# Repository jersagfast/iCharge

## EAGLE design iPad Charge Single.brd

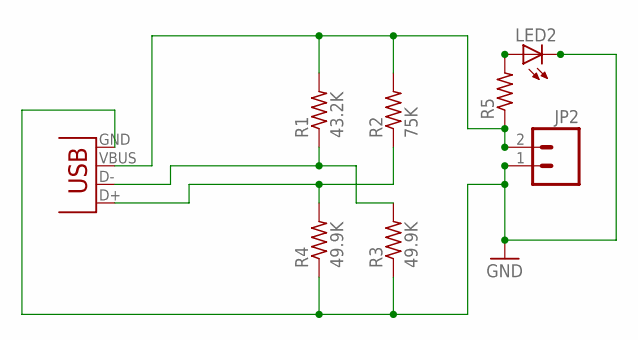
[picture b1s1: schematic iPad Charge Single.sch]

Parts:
JP2: M023.5MM; SCREWTERMINAL-3.5MM-2
LED2: LEDCHIP-LED0805; CHIP-LED0805
R1: 43.2K; R0805
R2: 75K; R0805
R3, R4: 49.9K; R0805
R5: R-US_R0805; R0805
X1: USB-A-S

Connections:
GND: JP2.1, LED2.C, R3.1, R4.1, X1.GND
unnamed: JP2.2, R1.2, R2.2, R5.1, X1.VBUS
unnamed: LED2.A, R5.2
unnamed: R2.1, R4.2, X1.D+
unnamed: R1.1, R3.2, X1.D-

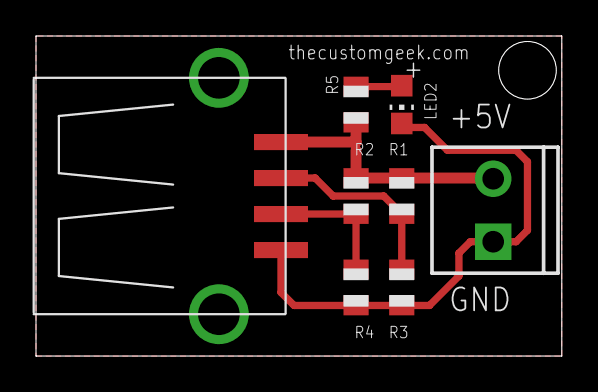
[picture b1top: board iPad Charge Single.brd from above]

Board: 2 copper layers, 29.2 x 17.8 mm, 9 parts (1 on the bottom side), 5 nets.

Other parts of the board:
U$4: OSHW-LOGO-M

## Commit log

2012-03-29 Updated BRD/SCH for 0805 Surface Mount parts, added a quote/BOM XLS
2012-03-29 Just added a junction or two for clarification fun.
